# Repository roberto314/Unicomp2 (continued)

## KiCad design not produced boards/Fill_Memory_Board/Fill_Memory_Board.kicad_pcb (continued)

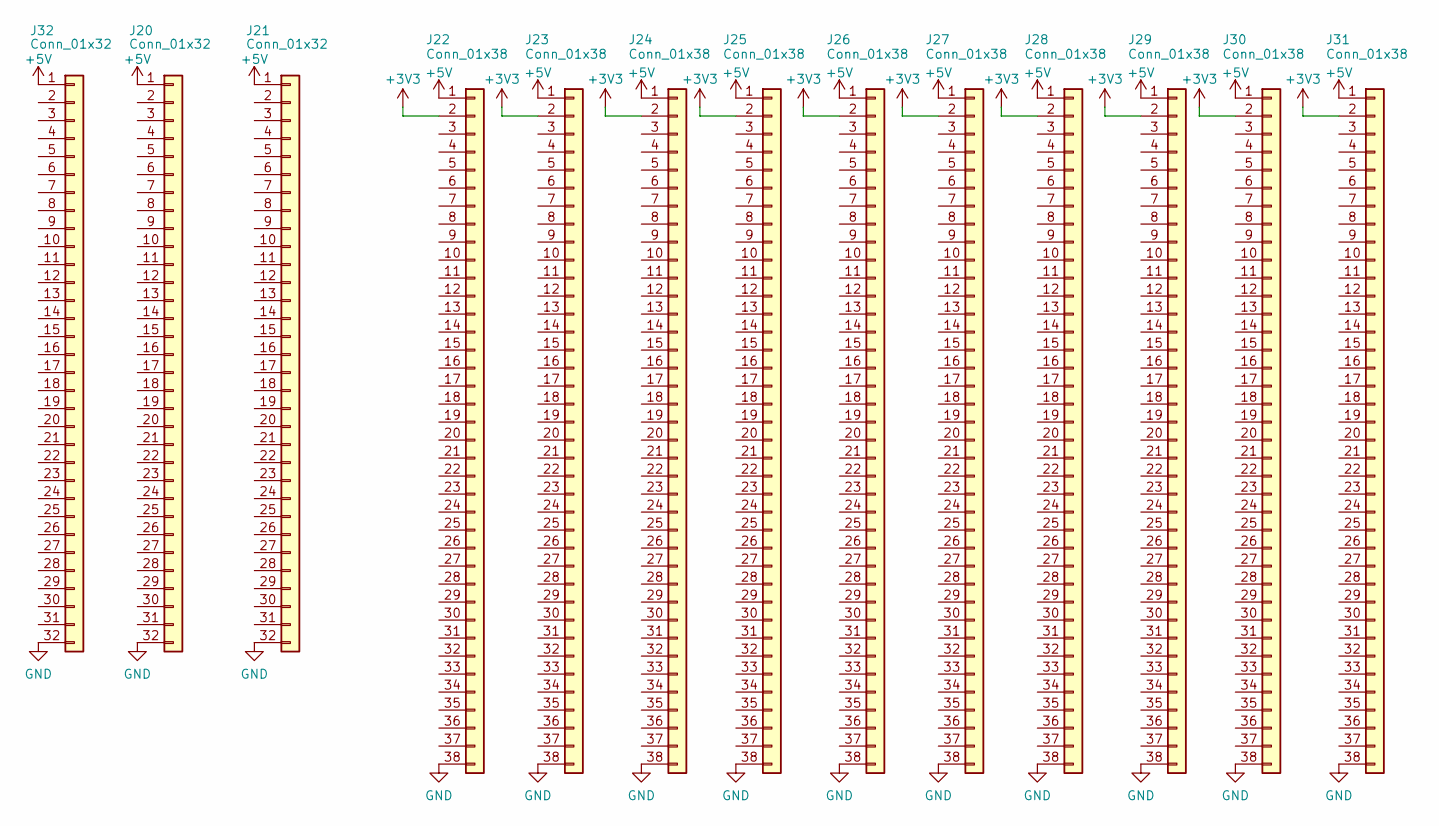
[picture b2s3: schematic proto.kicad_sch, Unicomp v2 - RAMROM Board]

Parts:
J20, J21, J32: Conn_01x32; PinHeader_1x32_P2.54mm_Vertical
J22, J23, J24, J25, J26, J27, J28, J29, J30, J31: Conn_01x38; PinHeader_1x38_P2.54mm_Vertical

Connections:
+3V3: J22.2, J23.2, J24.2, J25.2, J26.2, J27.2, J28.2, J29.2, J30.2, J31.2; also elsewhere on the board
+5V: J20.1, J21.1, J22.1, J23.1, J24.1, J25.1, J26.1, J27.1, J28.1, J29.1, J30.1, J31.1, J32.1; also elsewhere on the board
GND: J20.32, J21.32, J22.38, J23.38, J24.38, J25.38, J26.38, J27.38, J28.38, J29.38, J30.38, J31.38, J32.32; also elsewhere on the board

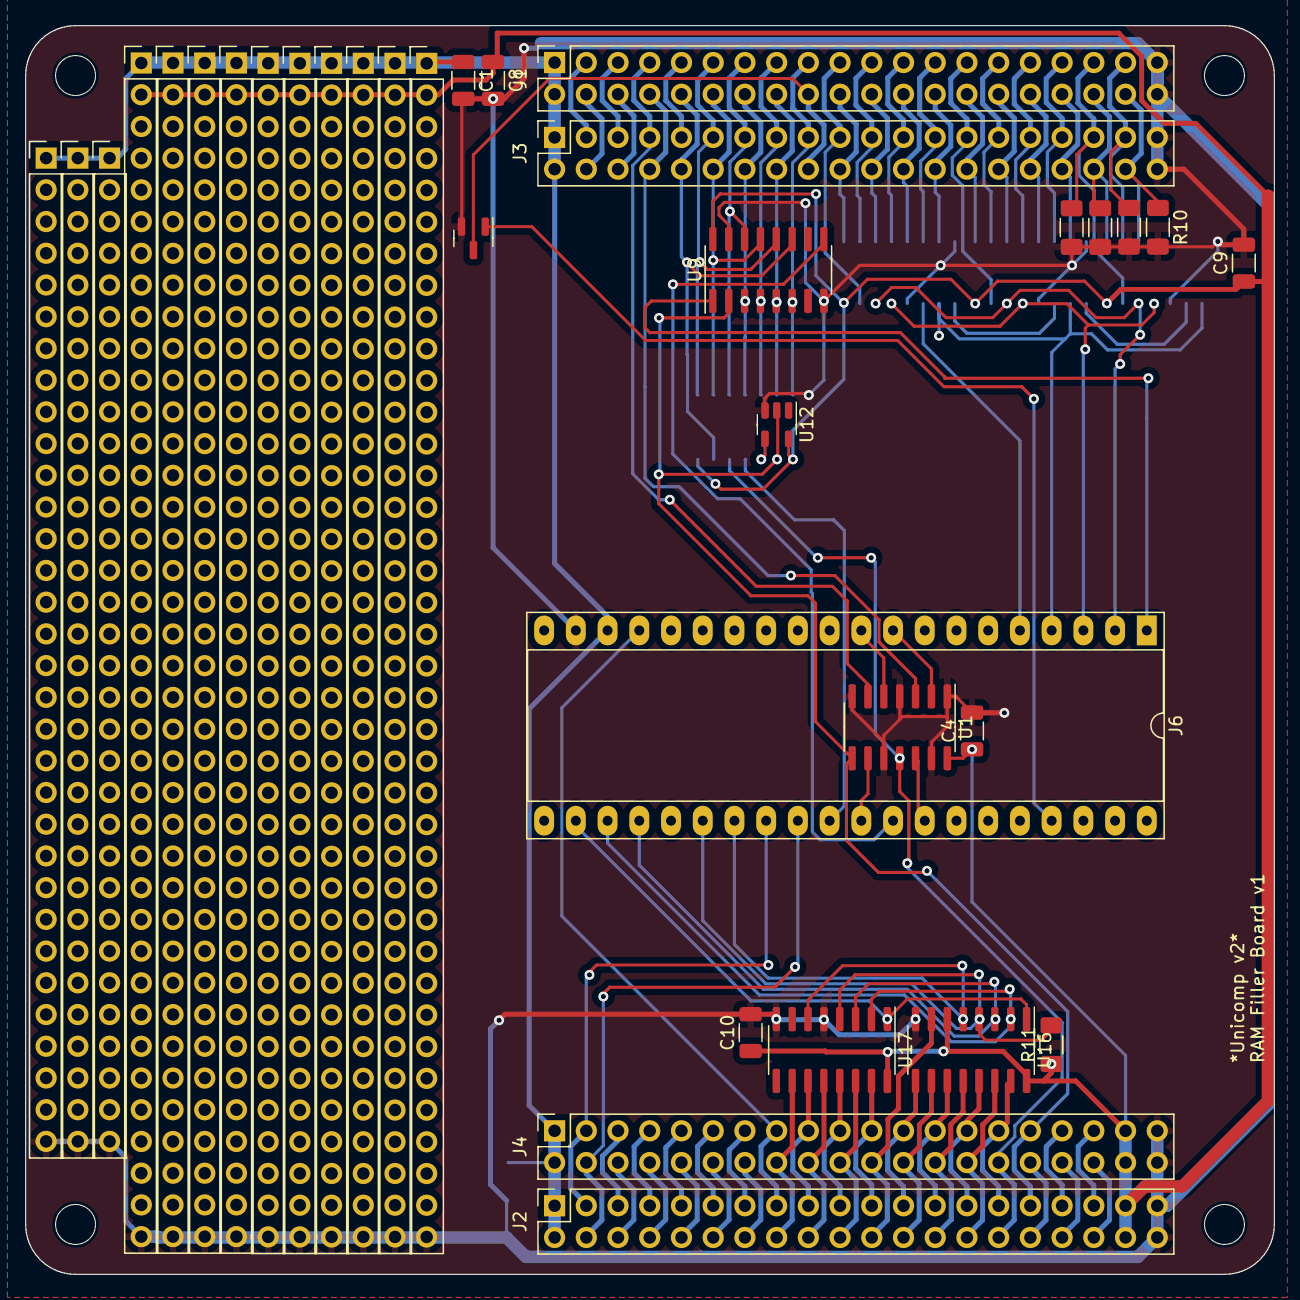
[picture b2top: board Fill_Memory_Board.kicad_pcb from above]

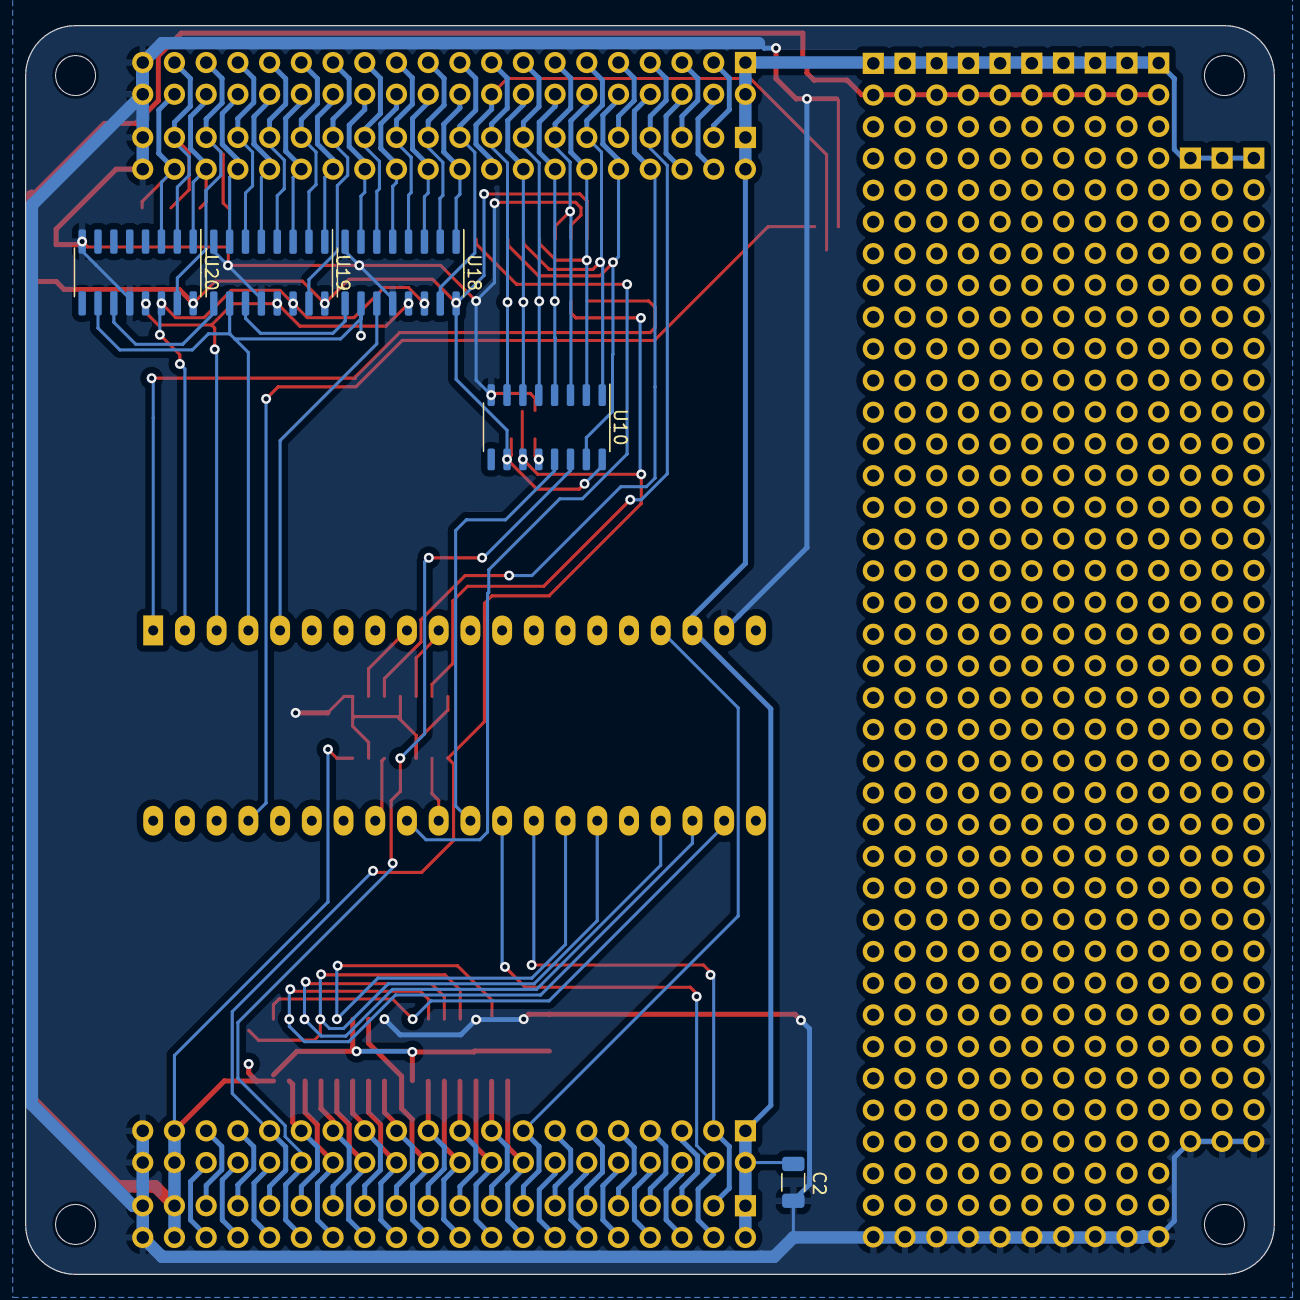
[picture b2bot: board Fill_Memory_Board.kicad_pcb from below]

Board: 2 copper layers, 100.0 x 100.0 mm, 43 parts (5 on the bottom side), 93 nets.

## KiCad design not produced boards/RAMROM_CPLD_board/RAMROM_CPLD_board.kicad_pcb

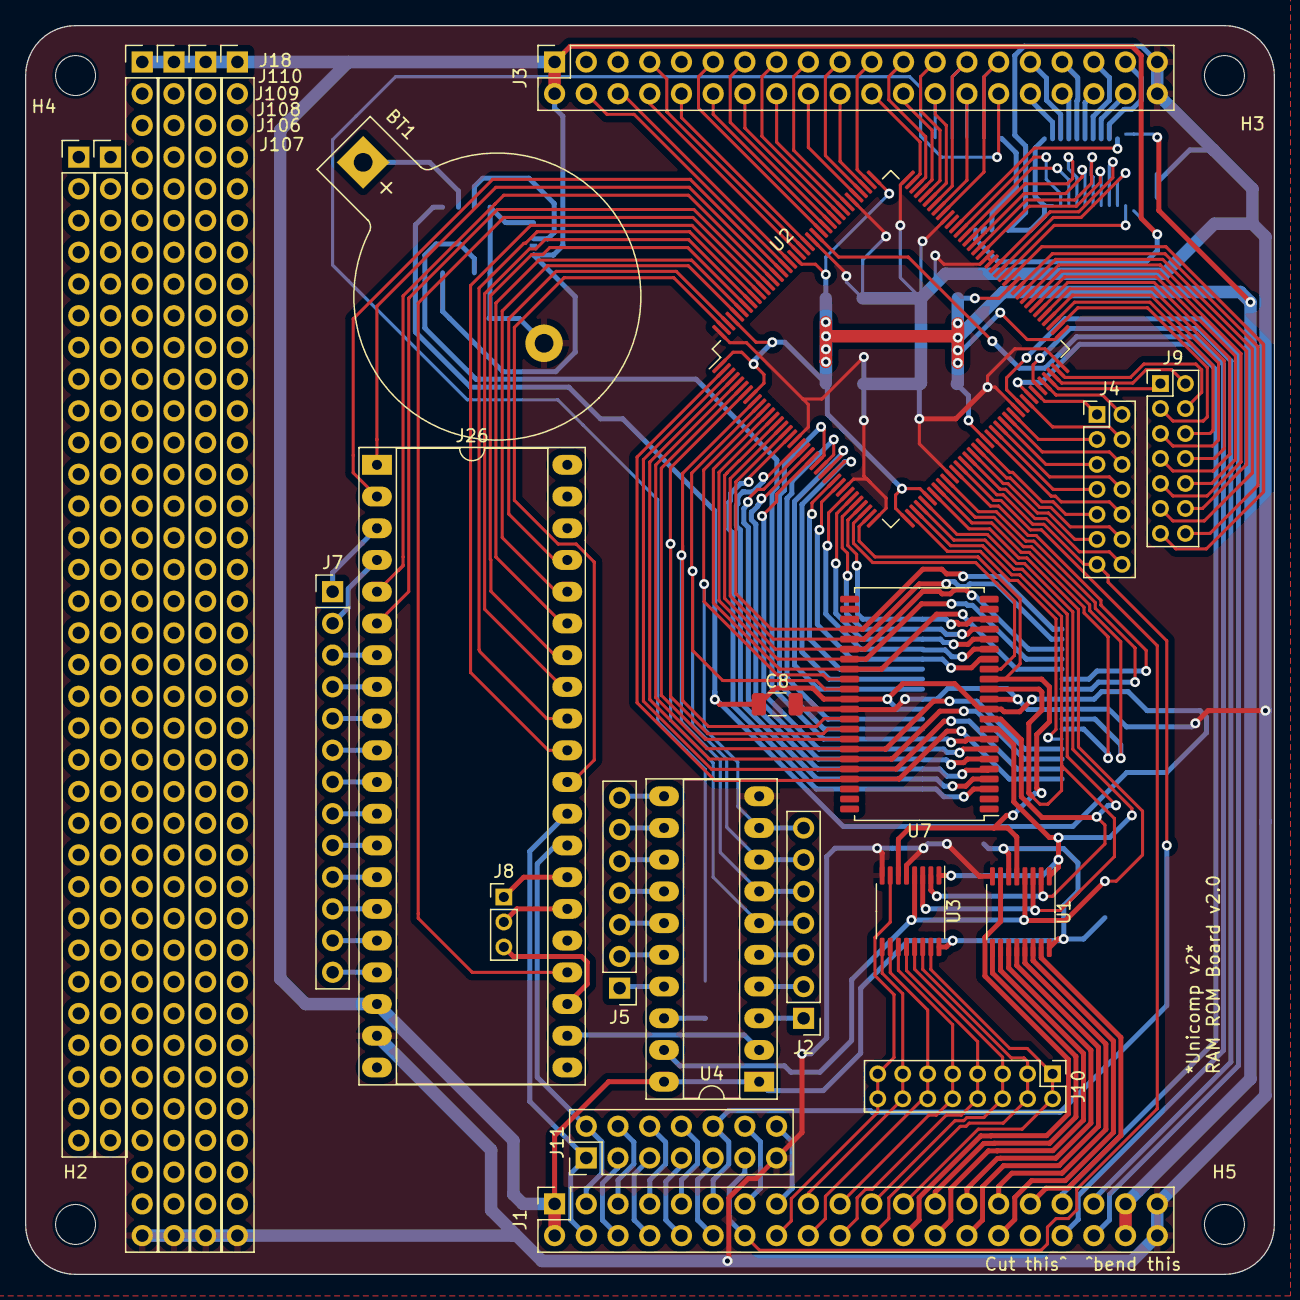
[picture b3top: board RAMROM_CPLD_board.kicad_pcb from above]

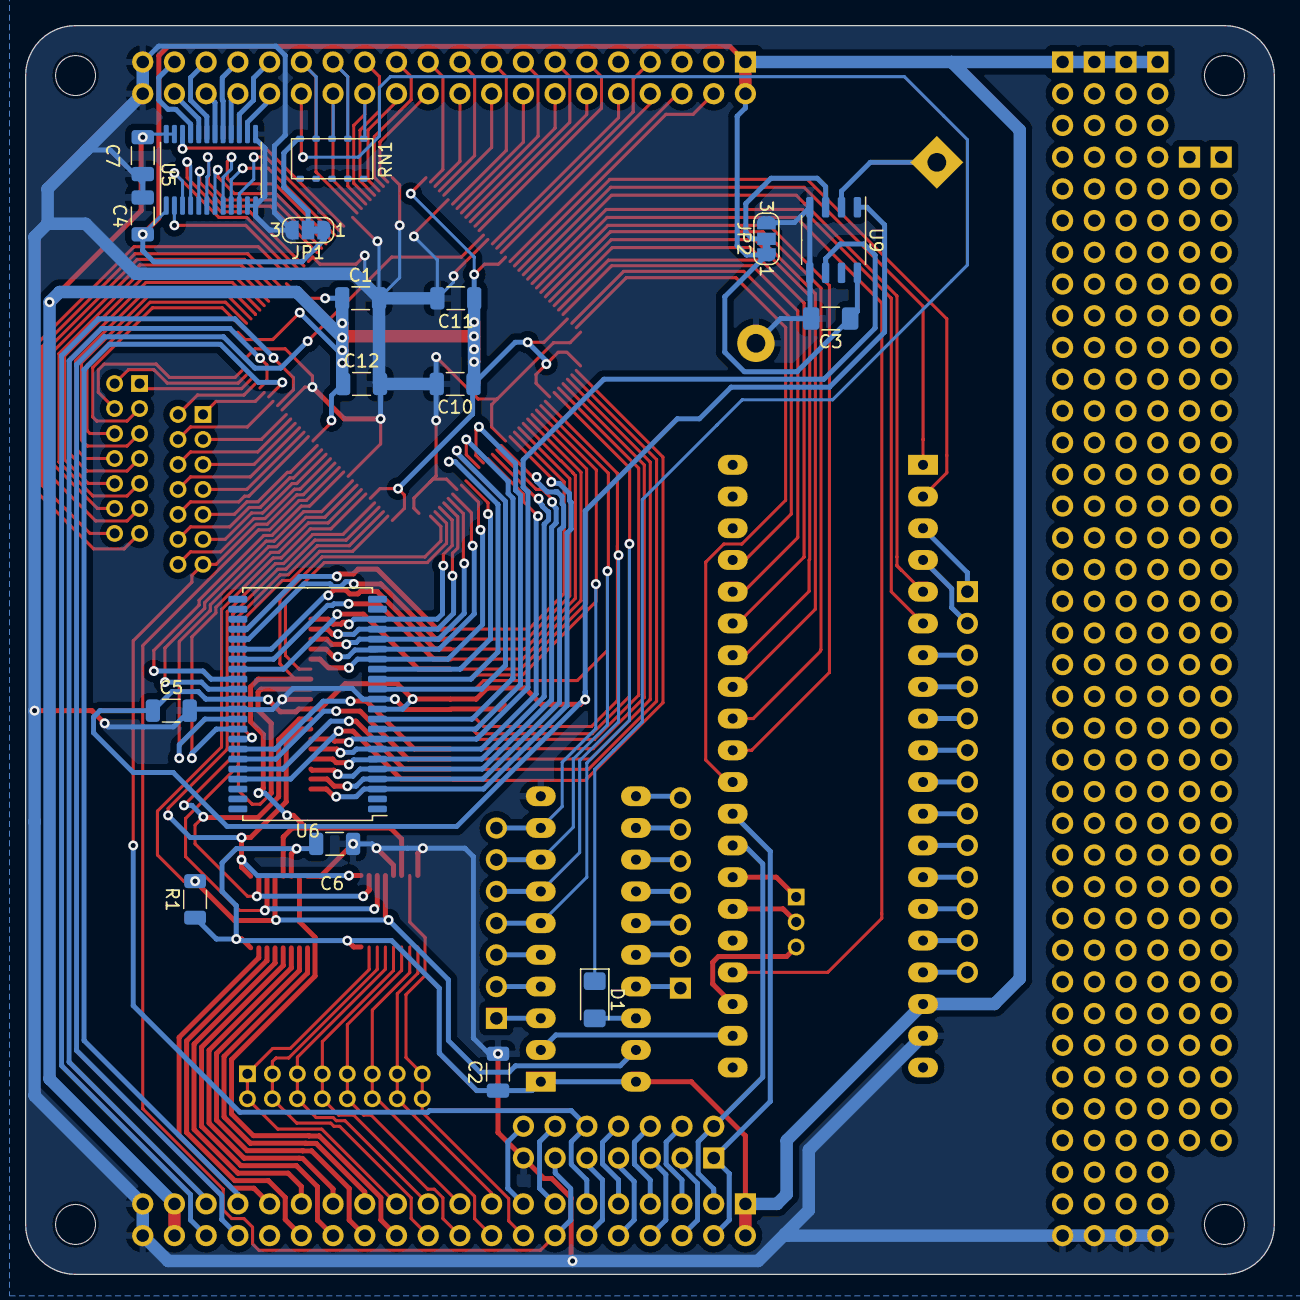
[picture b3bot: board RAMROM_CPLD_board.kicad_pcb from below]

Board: 2 copper layers, 100.0 x 100.0 mm, 46 parts (18 on the bottom side), 192 nets.

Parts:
BT1: Battery_Cell; BatteryHolder_Keystone_103_1x20mm
C1, C2, C4, C5, C6, C7, C8, C10, C11, C12: 100n; C_1206_3216Metric
C3: 100n; C_1206_3216Metric_Pad1.33x1.80mm_HandSolder
D1: 1N4148; D_1206_3216Metric_Pad1.42x1.75mm_HandSolder
H2, H3, H4, H5: MountingHole; MountingHole_3.2mm_M3
J1, J3: BUS; PinSocket_2x20_P2.54mm_Vertical
J2, J5: Conn_01x07; PinHeader_1x07_P2.54mm_Vertical
J4, J9: Conn_02x07_Counter_Clockwise; PinHeader_2x07_P2.00mm_Vertical
J7: Conn_01x13; PinHeader_1x13_P2.54mm_Vertical
J8: Conn_01x03; PinHeader_1x03_P2.00mm_Vertical
J10: CS_Breakout; PinHeader_2x08_P2.00mm_Vertical
J11: BO2; PinHeader_2x07_P2.54mm_Vertical
J18, J108, J109, J110: Conn_01x38_Male; PinHeader_1x38_P2.54mm_Vertical
J26: STM32F411; DIP-40_W15.24mm_Socket_LongPads
J106, J107: Conn_01x32; PinHeader_1x32_P2.54mm_Vertical
JP1: Jumper_3_Bridged12; SolderJumper-3_P1.3mm_Bridged12_RoundedPad1.0x1.5mm_NumberL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
JP2: ThresVolt; SolderJumper-3_P1.3mm_Bridged12_RoundedPad1.0x1.5mm_NumberL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
R1: 10k; R_1206_3216Metric
RN1: R_NET_8_SMD; R_Net2512_6.4x3.1_P1.27
U1, U3: 74AC138; TSSOP-16_4.4x5mm_P0.65mm
U2: XC95144XL-TQ144; TQFP-144_20x20mm_P0.5mm
U4: 74HCT245; DIP-20_W7.62mm_Socket_LongPads
U5: 74LVC4245; TSSOP-24_4.4x7.8mm_P0.65mm
U6, U7: IS61C5128AL-10TLI; TSOP-II-44_10.16x18.41mm_P0.8mm
U9: MXD1210; SOP-8_3.9x4.9mm_P1.27mm

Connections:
+3V3: C1.1, C7.1, C10.1, C11.1, C12.1, J1.37, J1.38, U2.1 (VCCIO), U2.8 (VCCINT), U2.37 (VCCIO), U2.42 (VCCINT), U2.55 (VCCIO), U2.73 (VCCIO), U2.84 (VCCINT), U2.109 (VCCIO), U2.127 (VCCIO), U2.141 (VCCINT), U5.23 (VCCB), U5.24 (VCCB)
+5V: C2.1, C3.1, C4.1, C6.1, J1.1, J1.2, J3.1, J3.2, J18.1, J26.18, J108.1, J109.1, J110.1, JP1.1 (A), JP2.1 (A), R1.1, U1.6 (E3), U1.16 (VCC), U3.16 (VCC), U4.1 (A->B), U4.20 (VCC), U5.1 (VCCA), U9.8 (VCI)
/A0: J3.10, U2.124
/A1: J3.11, U2.121
/A2: J3.12, U2.120
/A3: J3.13, U2.119
/A4: J3.14, U2.118
/A5: J3.15, U2.117
/A6: J3.16, U2.116
/A7: J3.17, U2.115
/A8: J3.18, U2.113
/A9: J3.19, U2.112
/A10: J3.20, U2.111
/A11: J3.21, U2.110
/A12: J3.22, U2.107
/A13: J3.23, U2.106
/A14: J3.24, U2.105
/A15: J3.25, U2.104
/A16: J3.26, RN1.1 (R4), U2.103
/A17: J3.27, RN1.2 (R1), U2.102
/A18: J3.28, RN1.3 (R2), U2.101
/A19: J3.29, RN1.4 (R3), U2.100
/B2: J26.36, U2.140
/B3: J7.7, J26.11
/B4: J7.8, J26.12
/B5: J7.9, J26.13
/B6: J7.10, J26.14
/B7: J7.11, J26.15
/B8: J7.12, J26.16
/B9: J7.13, J26.17
/B10: J26.37, U2.142
/B14: J7.1, J26.3
/B15: J7.2, J26.4
/C14: J8.3, J26.23
/CD0: U2.96, U5.10 (A7)
/CD1: U2.95, U5.9 (A6)
/CD2: U2.94, U5.8 (A5)
/CD3: U2.93, U5.7 (A4)
/CD4: U2.92, U5.6 (A3)
/CD5: U2.91, U5.5 (A2)
/CD6: U2.88, U5.4 (A1)
/CD7: U2.87, U5.3 (A0)
/CLKF: J1.14, J11.11, U2.49
/CLKS: J1.13, J11.12
/CNT: J26.1, U2.131
/CPLD0: J4.11, U2.52
/CPLD1: J4.12, U2.53
/CPLD2: J4.9, U2.54
/CPLD3: J4.10, U2.56
/CPLD4: J4.7, U2.57
/CPLD5: J4.8, U2.58
/CPLD6: J4.5, U2.59
/CPLD7: J4.6, U2.60
/CPLD8: J4.3, U2.61
/CPLD9: J4.4, U2.64
/CPLD10: J4.1, U2.66
/CPLD11: J4.2, U2.68
/CPLD12: J9.1, U2.69
/CPLD13: J9.2, U2.70
/CPLD14: J9.4, U2.71
/CPLD15: J9.3, U2.74
/CPLD16: J9.6, U2.75
/CPLD17: J9.5, U2.76
/CPLD18: J9.8, U2.77
/CPLD19: J9.7, U2.78
/CPLD20: J9.10, U2.79
/CPLD21: J9.9, U2.80
/CPLD22: J9.12, U2.81
/CPLD23: J9.11, U2.82
/CPLD24: J9.14, U2.83
/CPLD25: J9.13, U2.85
/CPLD28: J4.14, U2.51
/D0: J3.32, U5.14 (B7)
/D1: J3.31, U5.15 (B6)
/D2: J3.34, U5.16 (B5)
/D3: J3.33, U5.17 (B4)
/D4: J3.36, U5.18 (B3)
/D5: J3.35, U5.19 (B2)
/D6: J3.38, U5.20 (B1)
/D7: J3.37, U5.21 (B0)
/DDIR: U2.86, U5.2 (A->B)
/IA0: U2.17, U6.3 (A0), U7.3 (A0)
/IA1: U2.19, U6.4 (A1), U7.4 (A1)
/IA2: U2.20, U6.5 (A2), U7.5 (A2)
/IA3: U2.21, U6.6 (A3), U7.6 (A3)
/IA4: U2.22, U6.7 (A4), U7.7 (A4)
/IA5: U2.28, U6.16 (A5), U7.16 (A5)
/IA6: U2.30 (I/O/GCK1), U6.17 (A6), U7.17 (A6)
/IA7: U2.31, U6.18 (A7), U7.18 (A7)
/IA8: U2.32 (I/O/GCK2), U6.19 (A8), U7.19 (A8)
/IA9: U2.33, U6.20 (A9), U7.20 (A9)
/IA10: U2.16, U6.26 (A10), U7.26 (A10)
/IA11: U2.15, U6.27 (A11), U7.27 (A11)
/IA12: U2.14, U6.28 (A12), U7.28 (A12)
/IA13: U2.13, U6.29 (A13), U7.29 (A13)
/IA14: U2.12, U6.30 (A14), U7.30 (A14)
/IA15: U2.5 (I/O/GTS1), U6.38 (A15), U7.38 (A15)
/IA16: U2.4, U6.39 (A16), U7.39 (A16)
/IA17: U2.3 (I/O/GTS4), U6.40 (A17), U7.40 (A17)
/IA18: U2.2 (I/O/GTS3), U6.41 (A18), U7.41 (A18)
/ID0: U2.23, U6.9 (I/O0)
/ID1: U2.24, U6.10 (I/O1)
/ID2: U2.25, U6.13 (I/O2)
/ID3: U2.26, U6.14 (I/O3)
/ID4: U2.48, U6.31 (I/O4)
/ID5: U2.46, U6.32 (I/O5)
/ID6: U2.45, U6.35 (I/O6)
/ID7: U2.44, U6.36 (I/O7)
/ID8: U1.1 (A0), U2.41, U3.1 (A0), U7.9 (I/O0)
/ID9: U1.2 (A1), U2.40, U3.2 (A1), U7.10 (I/O1)
/ID10: U1.3 (A2), U2.39, U3.3 (A2), U7.13 (I/O2)
/ID11: U1.5 (E2), U2.35, U3.6 (E3), U7.14 (I/O3)
/ID12: J2.7, U2.11, U4.9 (A7), U7.31 (I/O4)
/ID13: J2.6, U2.10, U4.8 (A6), U7.32 (I/O5)
/ID14: J2.5, U2.9, U4.7 (A5), U7.35 (I/O6)
/ID15: J2.4, U2.7, U4.6 (A4), U7.36 (I/O7)
/LATCH: J26.35, U2.139
/PH0: J1.11, J4.13, J11.10, U2.50
/PHI2_ext: J3.4, U2.129
/RES0: J1.7, J11.6
/RES1: J1.9, J11.8
/RES2: J1.15, J11.14
/RX2: J1.3, J11.2, J26.28
/RX3: J1.5, J11.4
/RX_3V: J1.10, J11.7
/R/~W_ext: J3.6, U2.128
/TCK: J1.35, U2.67 (TCK)
/TDI: J1.36, U2.63 (TDI)
/TDO: J1.34, U2.122 (TDO)
/TMS: J1.33, U2.65 (TMS)
/TX2: J1.4, J11.1, J26.29
/TX3: J1.6, J11.3
/TX_3V: J1.8, J11.5
/UMISO: J26.32, U2.136
/UMOSI: J26.33, U2.137
/USCK: J26.31, U2.135
/Vdd: C5.1, C8.1, U6.11 (VDD), U6.33 (VDD), U7.11 (VDD), U7.33 (VDD), U9.1 (VCO)
/uA0: J8.2, J26.26
/uA1: J8.1, J26.27
/uA4: J26.30, U2.143 (I/O/GSR)
/uA10: J7.3, J26.7
/uA11: J7.4, J26.8
/uA12: J7.5, J26.9
/uA15: J7.6, J26.10
/~CS0: J1.31, U1.15 (O0)
/~CS1: J1.30, U1.14 (O1)
/~CS2: J1.29, U1.13 (O2)
/~CS3: J1.28, U1.12 (O3)
/~CS4: J1.27, U1.11 (O4)
/~CS5: J1.26, U1.10 (O5)
/~CS6: J1.25, U1.9 (O6)
/~CS7: J1.24, U1.7 (O7)
/~CS8: J1.23, J10.1, J10.2, U3.15 (O0)
/~CS9: J1.22, J10.3, J10.4, U3.14 (O1)
/~CS10: J1.21, J10.5, J10.6, U3.13 (O2)
/~CS11: J1.20, J10.7, J10.8, U3.12 (O3)
/~CS12: J1.19, J10.9, J10.10, U3.11 (O4)
/~CS13: J1.18, J10.11, J10.12, U3.10 (O5)
/~CS14: J1.17, J10.13, J10.14, U3.9 (O6)
/~CS15: J1.16, J10.15, J10.16, U3.7 (O7)
/~DOE: U2.97, U5.22 (CE)
/~EXTRST: J26.22, U4.2 (A0)
/~LOAD: J26.34, U2.138
/~MRC: J26.2, U2.130
/~MRD: J3.7, U2.125
/~MWR: J3.8, U2.126
/~OE1: U2.38 (I/O/GCK3), U6.37 (~OE)
/~OE2: U2.6 (I/O/GTS2), U7.37 (~OE)
/~OVR: J26.24, U2.134
/~PH0: J1.12, J11.9
/~PLD: J26.6, U2.133
/~RST: D1.1 (K), J3.30
/~UWE: J26.5, U2.132
/~WE1: U2.27, U6.15 (~WE)
/~WE2: U2.34, U7.15 (~WE)
/~extCS: R1.2, U1.4 (E1), U2.43, U3.4 (E1), U4.19 (CE)
GND: BT1.2 (-), C1.2, C2.2, C3.2, C4.2, C5.2, C6.2, C7.2, C8.2, C10.2, C11.2, C12.2, J1.39, J1.40, J3.39, J3.40, J11.13, J18.38, J26.19, J108.38, J109.38, J110.38, JP1.3 (B), JP2.3 (B), U1.8 (GND), U2.18 (GND), U2.29 (GND), U2.36 (GND), U2.47 (GND), U2.62 (GND), U2.72 (GND), U2.89 (GND), U2.90 (GND), U2.99 (GND), U2.108 (GND), U2.114 (GND), U2.123 (GND), U2.144 (GND), U3.5 (E2), U3.8 (GND), U4.10 (GND), U5.11 (GND), U5.12 (GND), U5.13 (GND), U6.12 (GND), U6.34 (GND), U7.12 (GND), U7.34 (GND), U9.4 (GND), U9.5 (CEI)
unnamed: BT1.1 (+), U9.2 (VBATT1)
unnamed: D1.2 (A), U4.18 (B0)
unnamed: J2.1, U4.3 (A1)
unnamed: J2.2, U4.4 (A2)
unnamed: J2.3, U4.5 (A3)
unnamed: J5.1, U4.17 (B1)
unnamed: J5.2, U4.16 (B2)
unnamed: J5.3, U4.15 (B3)
unnamed: J5.4, U4.14 (B4)
unnamed: J5.5, U4.13 (B5)
unnamed: J5.6, U4.12 (B6)
unnamed: J5.7, U4.11 (B7)
unnamed: JP1.2 (C), RN1.5 (common)
unnamed: JP2.2 (C), U9.3 (TOL)
unnamed: U6.8 (~CE), U7.8 (~CE), U9.6 (CEO)
